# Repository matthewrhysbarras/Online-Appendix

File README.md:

# Online Appendix

Hardware and embedded firmware accompanying Matthew Rhys Barras's University of Hull PhD thesis, *Toward Mobile Neuroimaging: Design and Implementation of a Real-Time Multi-Modal EEG/fNIRS System*.

## Contents

| Directory | Contents | Thesis reference |
| --- | --- | --- |
| [Hardware](Hardware/README.md) | Revision 3 KiCad main-board project and July 2022 fabrication files | Chapter 3; Appendix A |
| [Firmware/STM32](Firmware/STM32/README.md) | STM32H743 acquisition firmware, 30 March 2022 snapshot | Chapter 4; Appendix B |
| [Firmware/ESP32](Firmware/ESP32/README.md) | ESP32-S2 communications firmware, 21 March 2022 snapshot | Chapter 4; Appendix B |

The study data path is STM32 acquisition → ESP32-S2 TCP forwarding → Python receiver → PC-side Lab Streaming Layer (LSL). The firmware retains the study packet format and optical schedule described in Chapter 4.

This repository covers the main-board design and study streaming firmware. The host application, recordings, mechanical designs and earlier development versions listed in the thesis are separate artefacts. Chapter 6's replay experiment is available as [Edge EEG Workload Classification v1.0.0](https://doi.org/10.5281/zenodo.20452990).

## Using the files

Start with the component READMEs for project layout, toolchains, configuration and build instructions. The hardware README explains how to open the KiCad project. These are research-prototype files; fabrication and participant use require appropriate engineering and safety review.

[PROVENANCE.md](PROVENANCE.md) records snapshot identifiers and preparation changes. [REVIEW.md](REVIEW.md) summarises verification. Existing attribution and licence notices are retained; see [LICENSING.md](LICENSING.md).

For citation, use the thesis title and author above, together with the relevant snapshot date or archive checksum. The thesis artefact access route is [matthewbarras.com/phd](https://matthewbarras.com/phd).

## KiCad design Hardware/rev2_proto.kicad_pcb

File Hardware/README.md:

# Revision 3 hardware

KiCad design files for the integrated EEG/fNIRS main board described in Chapter 3. The July 2022 revision 3 project retains its original filename, `rev2_proto`.

The board contains an STM32H743VIT6, an ESP32-S2-WROVER-I, four ADS1299 converters, power supplies, status indicators and interfaces for microSD storage and external optical hardware. The TLC5940 source driver connects through a daughterboard header. Tethered operation uses an external USB isolator.

## Open the project

Open `rev2_proto.kicad_pro` in KiCad, then open the schematic or PCB editor. The project contains:

- `rev2_proto.kicad_sch`: processors and board interfaces.
- `ADS1299.kicad_sch`, `ADS1299_B.kicad_sch`, `ADS1299_C.kicad_sch`, `ADS1299_D.kicad_sch`: converter sheets.
- `PowerSupplies.kicad_sch` and `Status_LEDs.kicad_sch`.
- `rev2_proto.kicad_pcb`: four-layer PCB layout.
- `Fabrication-2022-07-15/`: 13 Gerber and drill files covering copper, solder mask, paste, silkscreen, outline and plated/non-plated holes.

The project uses KiCad 6 format; the fabrication headers identify KiCad 6.0.4. Opening and exporting the project was also checked with KiCad 10.0.4. The supplied files remain in their original format.

Symbols and footprints are embedded, so the schematic and board can be inspected without restoring workstation-specific libraries. Library-based updates require the corresponding libraries. Optional external 3D models are not included, so the 3D view may be incomplete.

## Revision and use

The selected PCB is the 15 July 2022, 15:24 copy, supplied with the July fabrication outputs. Snapshot hashes and the relationship to the earlier same-day archive are recorded in [PROVENANCE.md](../PROVENANCE.md).

The circuit, layout and fabrication files are unchanged. Preparation removed temporary project files, workstation paths and an obsolete reference URL. A layer-export comparison confirmed unchanged PCB geometry.

This is the main-board project; optical daughterboards, optode assemblies and enclosure parts are separate. A fitted-component BOM is not supplied. Before fabrication, check design rules, component selection, assembly requirements and manufacturing settings. The design is a research prototype, not a clinically certified device.

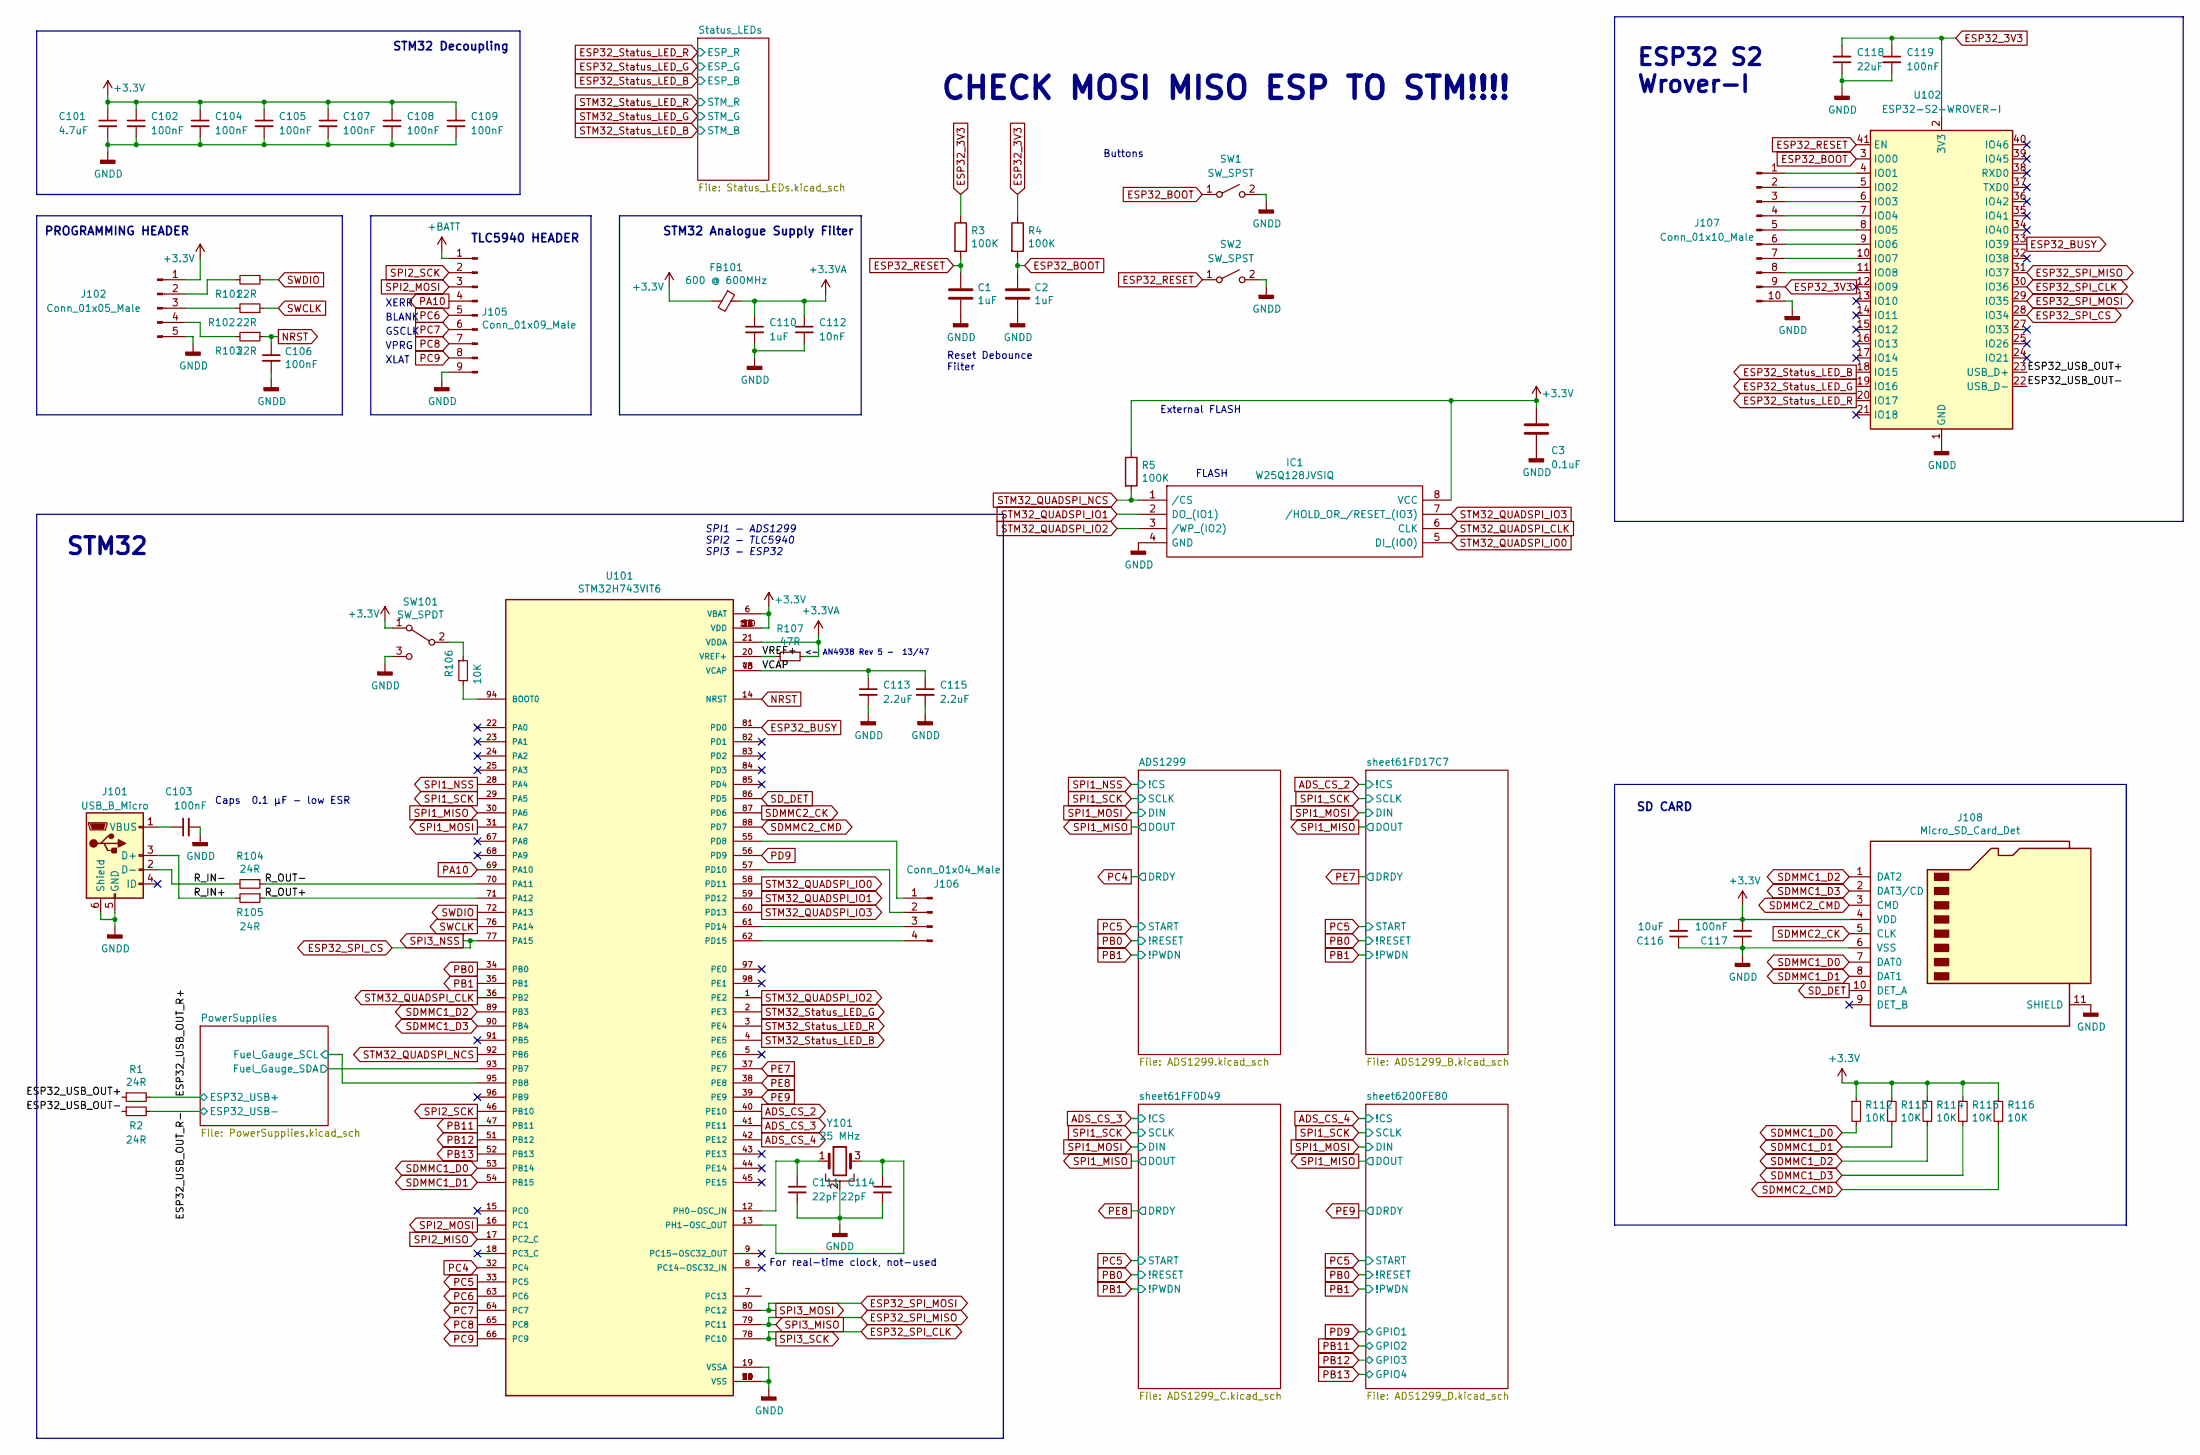
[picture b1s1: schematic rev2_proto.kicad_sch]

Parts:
C1, C2: 1uF; C_0402_1005Metric
C3: 0.1uF; C_0402_1005Metric
C101: 4.7uF; C_0805_2012Metric
C102, C103, C104, C105, C106, C107, C108, C109, C117, C119: 100nF; C_0805_2012Metric
C110: 1uF; C_0805_2012Metric
C111, C114: 22pF; C_0805_2012Metric
C112: 10nF; C_0805_2012Metric
C113, C115: 2.2uF; C_0805_2012Metric
C116: 10uF; C_0805_2012Metric
C118: 22uF; C_0805_2012Metric
FB101: 600 @ 600MHz; L_0805_2012Metric
IC1: W25Q128JVSIQ; SOIC127P790X216-8N; Mouser Part Number 454-W25Q128JVSIQ
J101: USB_B_Micro; USB_Micro-B_Wuerth_629105150521
J102: Conn_01x05_Male; PinHeader_1x05_P2.54mm_Vertical
J105: Conn_01x09_Male; PinHeader_1x09_P1.27mm_Vertical
J106: Conn_01x04_Male; PinHeader_1x04_P1.27mm_Vertical
J107: Conn_01x10_Male; PinHeader_1x10_P1.27mm_Vertical
J108: Micro_SD_Card_Det; microSD_HC_Molex_104031-0811
R1, R2, R104, R105: 24R; R_0805_2012Metric
R3, R4, R5: 100K; R_0402_1005Metric
R101, R102, R103: 22R; R_0805_2012Metric
R106, R112, R113, R114, R115, R116: 10K; R_0805_2012Metric
R107: 47R; R_0805_2012Metric
SW1, SW2: SW_SPST; SW_PUSH_6mm_H4.3mm
SW101: SW_SPDT; PinHeader_1x03_P2.54mm_Vertical
U101: STM32H743VIT6; QFP50P1600X1600X160-100N; PARTREV 7
U102: ESP32-S2-WROVER-I; ESP32-S2-WROVER
Y101: 25 MHz; Crystal_SMD_Abracon_ABM8G-4Pin_3.2x2.5mm

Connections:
+3.3VA: C110.1, C112.1, FB101.1, R107.1, U101.21 (VDDA)
+BATT: J105.1; also elsewhere on the board
/ESP32_USB_OUT+: R1.1, U102.23 (USB_D+)
/ESP32_USB_OUT-: R2.1, U102.22 (USB_D-)
/ESP32_USB_OUT_R+: R1.2; also elsewhere on the board
/ESP32_USB_OUT_R-: R2.2; also elsewhere on the board
/PowerSupplies/Fuel_Gauge_SCL: U101.95 (PB8); also elsewhere on the board
/PowerSupplies/Fuel_Gauge_SDA: U101.93 (PB7); also elsewhere on the board
/R_IN+: J101.3 (D+), R105.2
/R_IN-: J101.2 (D-), R104.2
/R_OUT+: R105.1, U101.71 (PA12)
/R_OUT-: R104.1, U101.70 (PA11)
/VCAP: C113.1, C115.1, U101.48 (VCAP), U101.73 (VCAP)
/VREF+: R107.2, U101.20 (VREF+)
ADS_CS_2: U101.40 (PE10); also elsewhere on the board
ADS_CS_3: U101.41 (PE11); also elsewhere on the board
ADS_CS_4: U101.42 (PE12); also elsewhere on the board
ESP32_3V3: C118.2, C119.1, J107.9, R3.1, R4.1, U102.2 (3V3); also elsewhere on the board
ESP32_BOOT: C2.1, R4.2, SW1.1 (A), U102.3 (IO00); also elsewhere on the board
ESP32_BUSY: U101.81 (PD0), U102.33 (IO39)
ESP32_RESET: C1.1, R3.2, SW2.1 (A), U102.41 (EN); also elsewhere on the board
ESP32_SPI_CLK: U101.78 (PC10), U102.30 (IO36)
ESP32_SPI_CS: U101.77 (PA15), U102.28 (IO34)
ESP32_SPI_MISO: U101.79 (PC11), U102.31 (IO37)
ESP32_SPI_MOSI: U101.80 (PC12), U102.29 (IO35)
ESP32_Status_LED_B: U102.18 (IO15); also elsewhere on the board
ESP32_Status_LED_G: U102.19 (IO16); also elsewhere on the board
ESP32_Status_LED_R: U102.20 (IO17); also elsewhere on the board
GNDA: C1.2, C2.2, C3.2, C101.2, C102.2, C103.2, C104.2, C105.2, C106.2, C107.2, C108.2, C109.2, C110.2, C111.2, C112.2, C113.2, C114.2, C115.2, C116.1, C117.1, C118.1, C119.2, IC1.4 (GND), J101.5 (GND), J101.6 (Shield), J102.5, J105.9, J107.10, J108.6 (VSS), J108.11 (SHIELD), SW1.2 (B), SW2.2 (B), SW101.3 (C), U101.10 (VSS), U101.19 (VSSA), U101.26 (VSS), U101.49 (VSS), U101.74 (VSS), U101.99 (VSS), U102.1 (GND), U102.26 (GND), U102.42 (GND), U102.43 (GND), Y101.2; also elsewhere on the board
NRST: C106.1, R103.1, U101.14 (NRST)
unnamed: C103.1, J101.1 (VBUS)
unnamed: C111.1, U101.12 (PH0-OSC_IN), Y101.1
unnamed: C114.1, U101.13 (PH1-OSC_OUT), Y101.3
unnamed: J102.2, R101.2
unnamed: J102.3, R102.2
unnamed: J102.4, R103.2
unnamed: J106.1, U101.55 (PD8)
unnamed: J106.2, U101.57 (PD10)
unnamed: J106.3, U101.61 (PD14)
unnamed: J106.4, U101.62 (PD15)
unnamed: J107.1, U102.4 (IO01)
unnamed: J107.2, U102.5 (IO02)
unnamed: J107.3, U102.6 (IO03)
unnamed: J107.4, U102.7 (IO04)
unnamed: J107.5, U102.8 (IO05)
unnamed: J107.6, U102.9 (IO06)
unnamed: J107.7, U102.10 (IO07)
unnamed: J107.8, U102.11 (IO08)
unnamed: R106.1, SW101.2 (B)
unnamed: R106.2, U101.94 (BOOT0)
PA10: J105.4, U101.69 (PA10)
PB0: U101.34 (PB0); also elsewhere on the board
PB1: U101.35 (PB1); also elsewhere on the board
PB11: U101.47 (PB11); also elsewhere on the board
PB12: U101.51 (PB12); also elsewhere on the board
PB13: U101.52 (PB13); also elsewhere on the board
PC4: U101.32 (PC4); also elsewhere on the board
PC5: U101.33 (PC5); also elsewhere on the board
PC6: J105.5, U101.63 (PC6)
PC7: J105.6, U101.64 (PC7)
PC8: J105.7, U101.65 (PC8)
PC9: J105.8, U101.66 (PC9)
PD9: U101.56 (PD9); also elsewhere on the board
PE7: U101.37 (PE7); also elsewhere on the board
PE8: U101.38 (PE8); also elsewhere on the board
PE9: U101.39 (PE9); also elsewhere on the board
SDMMC1_D0: J108.7 (DAT0), R112.2, U101.53 (PB14)
SDMMC1_D1: J108.8 (DAT1), R113.2, U101.54 (PB15)
SDMMC1_D2: J108.1 (DAT2), R114.2, U101.89 (PB3)
SDMMC1_D3: J108.2 (DAT3/CD), R115.2, U101.90 (PB4)
SDMMC2_CK: J108.5 (CLK), U101.87 (PD6)
SDMMC2_CMD: J108.3 (CMD), R116.2, U101.88 (PD7)
SD_DET: J108.10 (DET_A), U101.86 (PD5)
SPI1_MISO: U101.30 (PA6); also elsewhere on the board
SPI1_MOSI: U101.31 (PA7); also elsewhere on the board
SPI1_NSS: U101.28 (PA4); also elsewhere on the board
SPI1_SCK: U101.29 (PA5); also elsewhere on the board
SPI2_MISO: U101.17 (PC2_C)
SPI2_MOSI: J105.3, U101.16 (PC1)
SPI2_SCK: J105.2, U101.46 (PB10)
STM32_QUADSPI_CLK: IC1.6 (CLK), U101.36 (PB2)
STM32_QUADSPI_IO0: IC1.5 (DI_(IO0)), U101.58 (PD11)
STM32_QUADSPI_IO1: IC1.2 (DO_(IO1)), U101.59 (PD12)
STM32_QUADSPI_IO2: IC1.3 (/WP_(IO2)), U101.1 (PE2)
STM32_QUADSPI_IO3: IC1.7 (/HOLD_OR_/RESET_(IO3)), U101.60 (PD13)
STM32_QUADSPI_NCS: IC1.1 (/CS), R5.2, U101.92 (PB6)
STM32_Status_LED_B: U101.4 (PE5); also elsewhere on the board
STM32_Status_LED_G: U101.2 (PE3); also elsewhere on the board
STM32_Status_LED_R: U101.3 (PE4); also elsewhere on the board
SWCLK: R102.1, U101.76 (PA14)
SWDIO: R101.1, U101.72 (PA13)

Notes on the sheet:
SD CARD
CHECK MOSI MISO ESP TO STM!!!!
Buttons
VPRG
ESP32 S2 Wrover-I
XERR
FLASH
Reset Debounce Filter
SPI1 - ADS1299 SPI2 - TLC5940 SPI3 - ESP32
XLAT
For real-time clock, not-used
TLC5940 HEADER
External FLASH
BLANK
<- AN4938 Rev 5 - 13/47
STM32 Analogue Supply Filter
STM32 Decoupling
GSCLK
PROGRAMMING HEADER
Caps 0.1 μF - low ESR
STM32

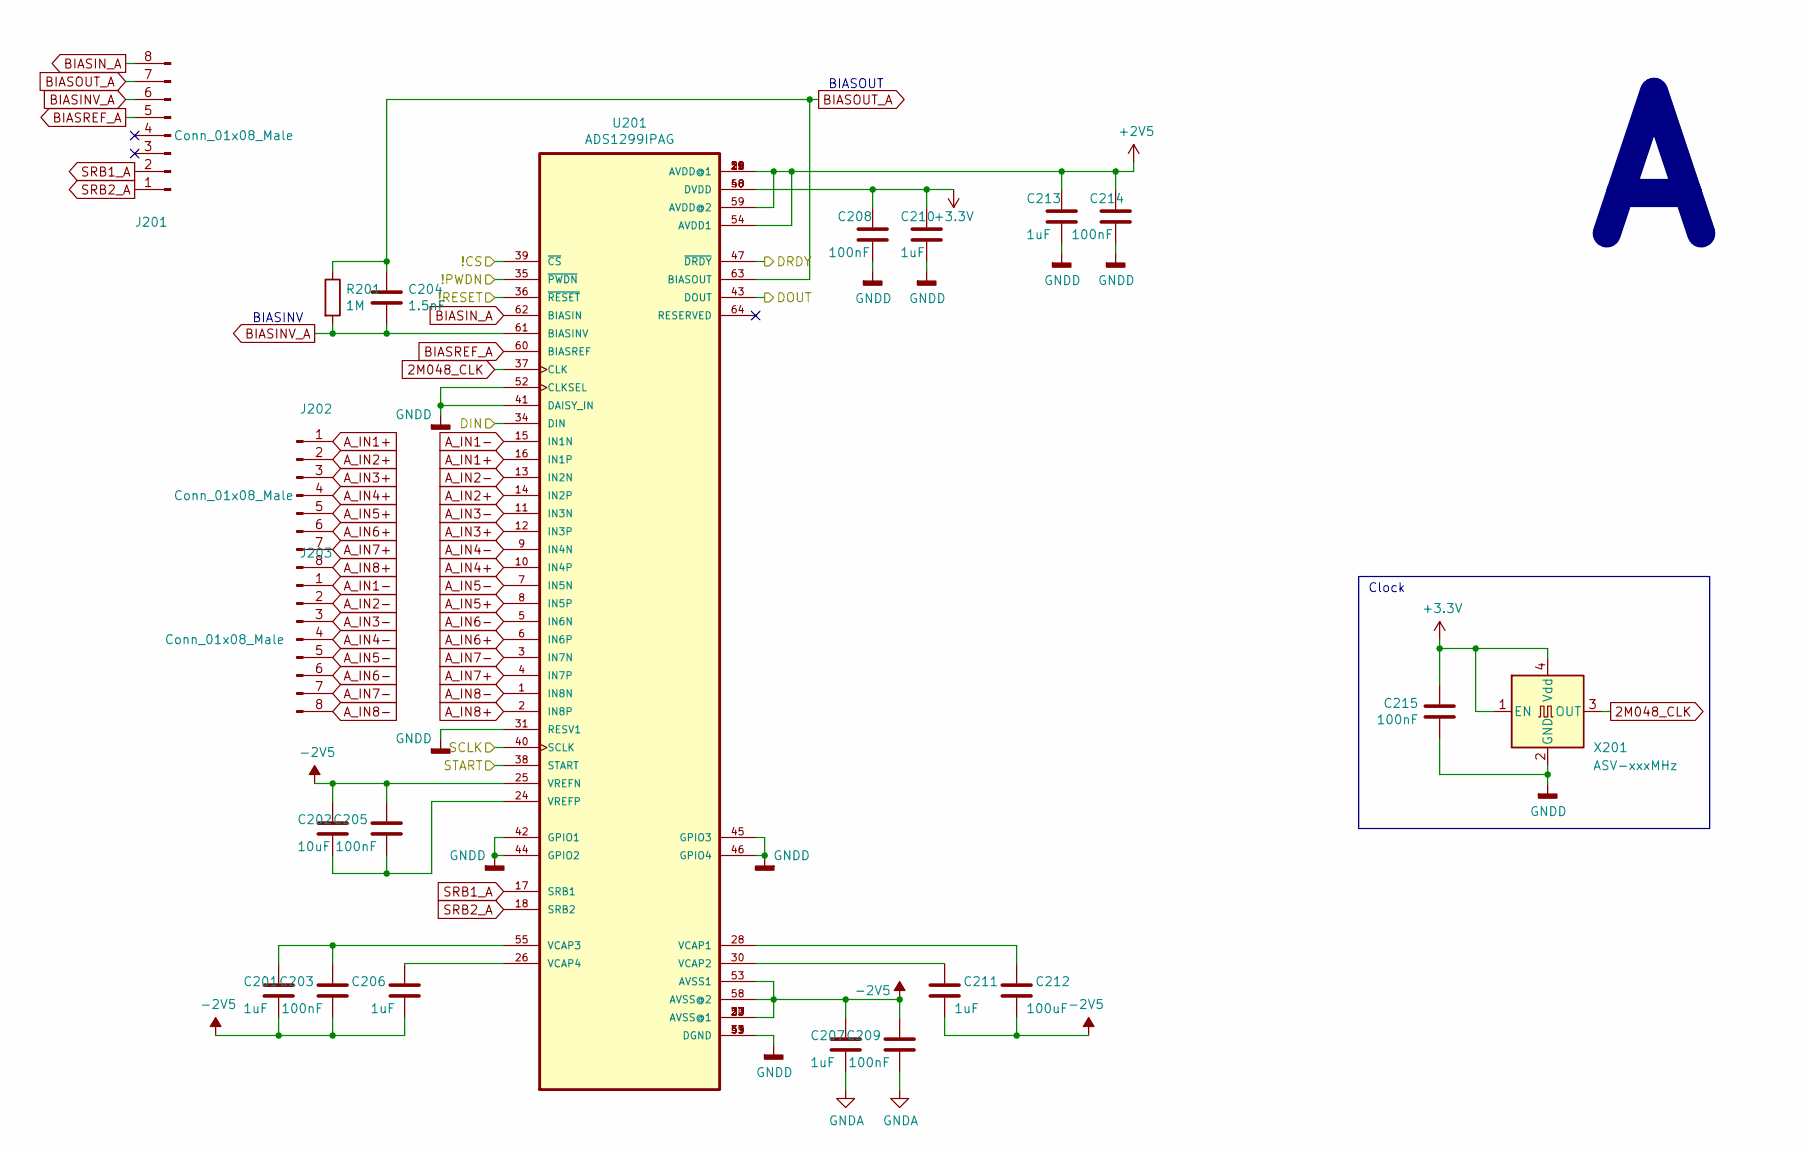
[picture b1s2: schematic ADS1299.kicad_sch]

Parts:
C201, C206, C207, C210, C211, C213: 1uF; C_0805_2012Metric
C202: 10uF; C_0805_2012Metric
C203, C205, C208, C209, C214, C215: 100nF; C_0805_2012Metric
C204: 1.5nF; C_0805_2012Metric
C212: 100uF; C_0805_2012Metric
J201, J202, J203: Conn_01x08_Male; PinHeader_1x08_P2.54mm_Vertical
R201: 1M; R_0805_2012Metric
U201: ADS1299IPAG; QFP50P1200X1200X120-64N
X201: ASV-xxxMHz; Oscillator_SMD_Abracon_ASV-4Pin_7.0x5.1mm

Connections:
2M048_CLK: U201.37 (CLK), X201.3 (OUT); also elsewhere on the board
+2V5: C213.1, C214.1, U201.19 (AVDD@1), U201.21 (AVDD@1), U201.22 (AVDD@1), U201.54 (AVDD1), U201.56 (AVDD@1), U201.59 (AVDD@2); also elsewhere on the board
-2V5: C201.2, C202.1, C203.2, C205.1, C206.2, C207.1, C209.1, C211.2, C212.2, U201.20 (AVSS@1), U201.23 (AVSS@1), U201.25 (VREFN), U201.32 (AVSS@1), U201.53 (AVSS1), U201.57 (AVSS@1), U201.58 (AVSS@2); also elsewhere on the board
A_IN1+: J202.1, U201.16 (IN1P)
A_IN1-: J203.1, U201.15 (IN1N)
A_IN2+: J202.2, U201.14 (IN2P)
A_IN2-: J203.2, U201.13 (IN2N)
A_IN3+: J202.3, U201.12 (IN3P)
A_IN3-: J203.3, U201.11 (IN3N)
A_IN4+: J202.4, U201.10 (IN4P)
A_IN4-: J203.4, U201.9 (IN4N)
A_IN5+: J202.5, U201.8 (IN5P)
A_IN5-: J203.5, U201.7 (IN5N)
A_IN6+: J202.6, U201.6 (IN6P)
A_IN6-: J203.6, U201.5 (IN6N)
A_IN7+: J202.7, U201.4 (IN7P)
A_IN7-: J203.7, U201.3 (IN7N)
A_IN8+: J202.8, U201.2 (IN8P)
A_IN8-: J203.8, U201.1 (IN8N)
BIASINV_A: C204.2, J201.6, R201.2, U201.61 (BIASINV)
BIASIN_A: J201.8, U201.62 (BIASIN)
BIASOUT_A: C204.1, J201.7, R201.1, U201.63 (BIASOUT)
BIASREF_A: J201.5, U201.60 (BIASREF)
GNDA: C207.2, C208.2, C209.2, C210.2, C213.2, C214.2, C215.1, U201.31 (RESV1), U201.33 (DGND), U201.41 (DAISY_IN), U201.42 (GPIO1), U201.44 (GPIO2), U201.45 (GPIO3), U201.46 (GPIO4), U201.49 (DGND), U201.51 (DGND), U201.52 (CLKSEL), X201.2 (GND); also elsewhere on the board
unnamed: C201.1, C203.1, U201.55 (VCAP3)
unnamed: C202.2, C205.2, U201.24 (VREFP)
unnamed: C206.1, U201.26 (VCAP4)
unnamed: C211.1, U201.30 (VCAP2)
unnamed: C212.1, U201.28 (VCAP1)
PB0: U201.36 (~RESET); also elsewhere on the board
PB1: U201.35 (~PWDN); also elsewhere on the board
PC4: U201.47 (~DRDY); also elsewhere on the board
PC5: U201.38 (START); also elsewhere on the board
SPI1_MISO: U201.43 (DOUT); also elsewhere on the board
SPI1_MOSI: U201.34 (DIN); also elsewhere on the board
SPI1_NSS: U201.39 (~CS); also elsewhere on the board
SPI1_SCK: U201.40 (SCLK); also elsewhere on the board
SRB1_A: J201.2, U201.17 (SRB1)
SRB2_A: J201.1, U201.18 (SRB2)

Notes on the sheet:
BIASOUT
BIASINV
Clock

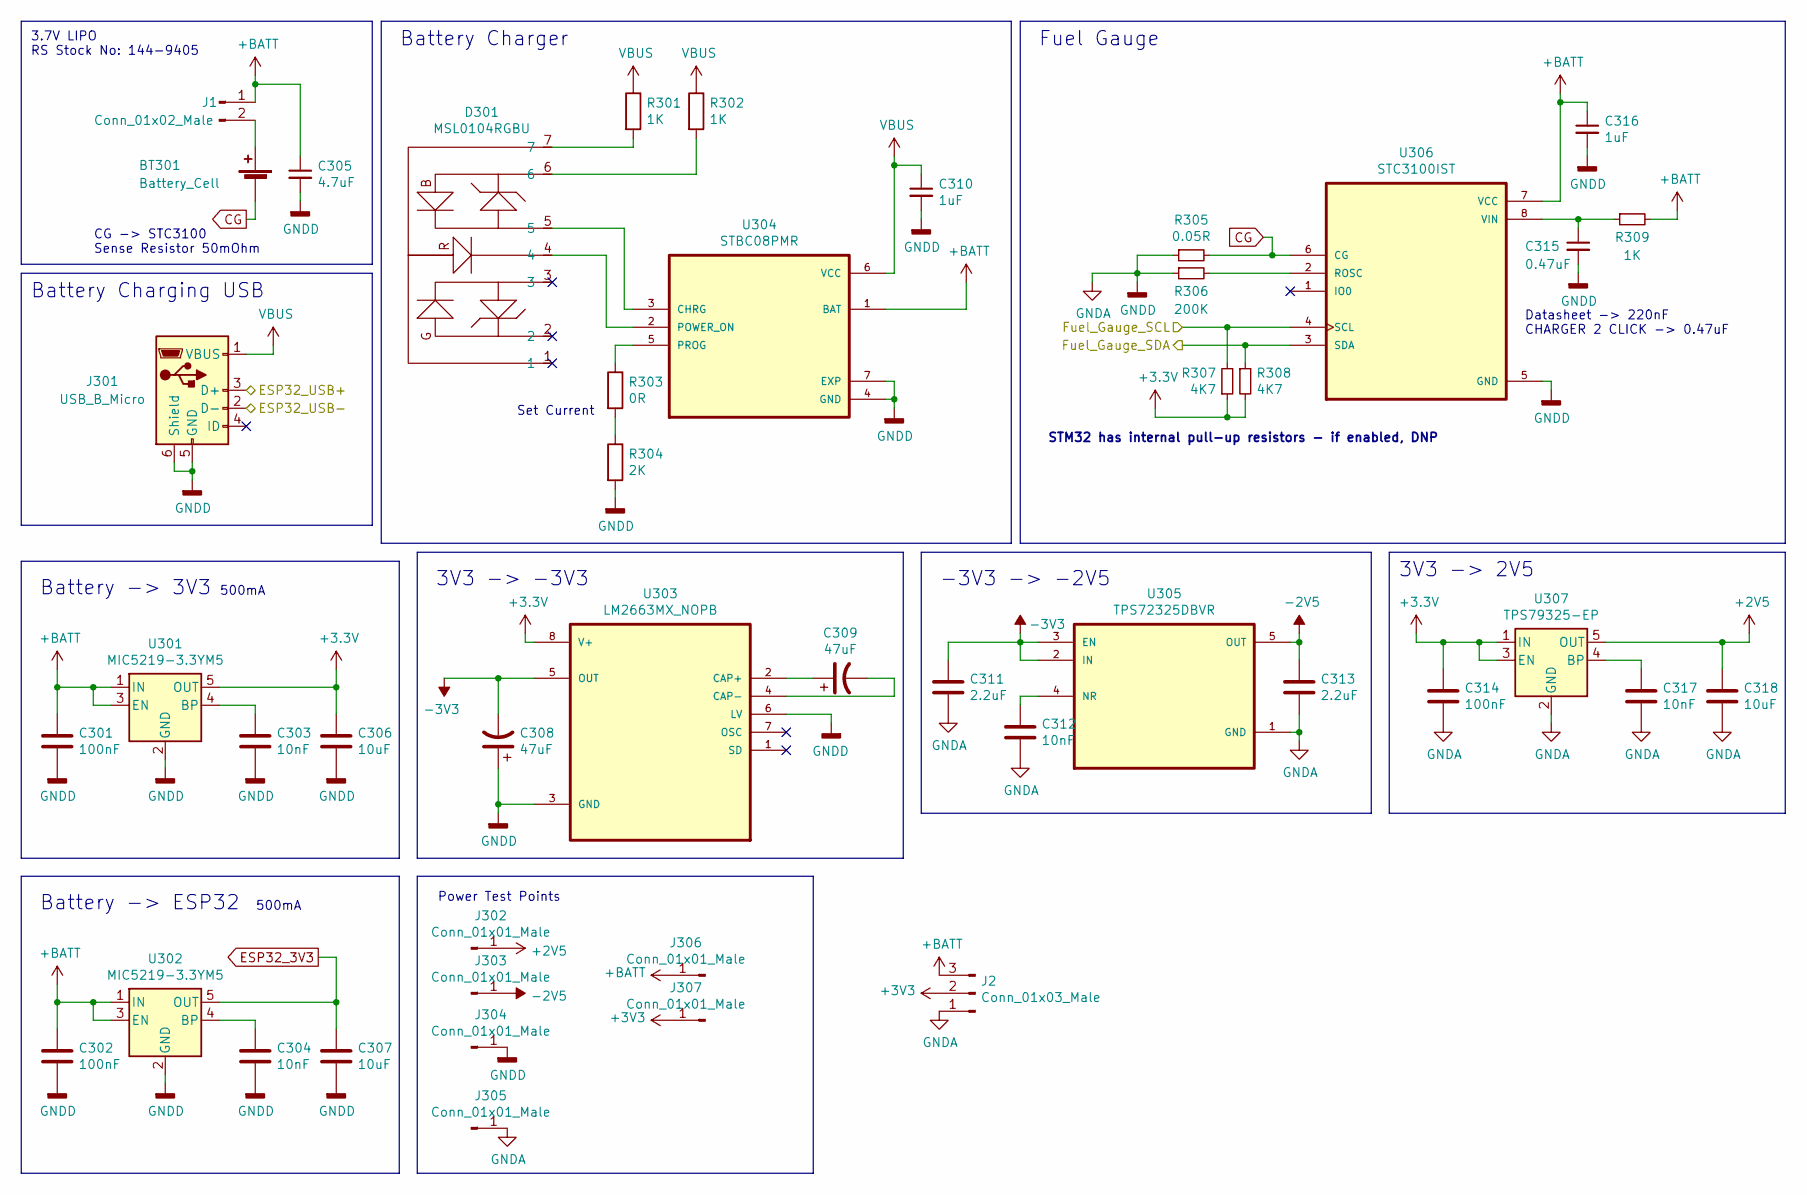
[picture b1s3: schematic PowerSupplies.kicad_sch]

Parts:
BT301: Battery_Cell; PinHeader_1x02_P2.54mm_Vertical
C301, C302, C314: 100nF; C_0805_2012Metric
C303, C304, C312, C317: 10nF; C_0805_2012Metric
C305: 4.7uF; C_0805_2012Metric
C306, C307, C318: 10uF; C_0805_2012Metric
C308, C309: 47uF; C_0805_2012Metric
C310, C316: 1uF; C_0805_2012Metric
C311, C313: 2.2uF; C_0805_2012Metric
C315: 0.47uF; C_0805_2012Metric
D301: MSL0104RGBU; MSL0104RGB
J1: Conn_01x02_Male; PinHeader_1x02_P2.54mm_Vertical
J2: Conn_01x03_Male; PinHeader_1x03_P2.54mm_Vertical
J301: USB_B_Micro; USB_Micro-B_Wuerth_629105150521
J302, J303, J305, J306, J307: Conn_01x01_Male; TestPoint_Pad_D1.0mm
J304: Conn_01x01_Male; TestPoint_Pad_3.0x3.0mm
R301, R302, R309: 1K; R_0805_2012Metric
R303: 0R; R_0805_2012Metric
R304: 2K; R_0805_2012Metric
R305: 0.05R; R_0805_2012Metric
R306: 200K; R_0805_2012Metric
R307, R308: 4K7; R_0805_2012Metric
U301, U302: MIC5219-3.3YM5; SOT-23-5
U303: LM2663MX_NOPB; SOIC127P599X175-8N
U304: STBC08PMR; SON95P300X300X100-7N; PARTREV 4
U305: TPS72325DBVR; SOT95P280X145-5N
U306: STC3100IST; SOIC65P490X110-8N
U307: TPS79325-EP; SOT-23-5

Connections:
+2V5: C318.1, J302.1, U307.5 (OUT); also elsewhere on the board
+BATT: C301.1, C302.1, C305.1, C316.1, J1.1, J2.3, J306.1, R309.2, U301.1 (IN), U301.3 (EN), U302.1 (IN), U302.3 (EN), U304.1 (BAT), U306.7 (VCC); also elsewhere on the board
-2V5: C313.1, J303.1, U305.5 (OUT); also elsewhere on the board
-3V3: C308.2, C311.1, U303.5 (OUT), U305.2 (IN), U305.3 (EN)
/ESP32_USB_OUT_R+: J301.3 (D+); also elsewhere on the board
/ESP32_USB_OUT_R-: J301.2 (D-); also elsewhere on the board
/PowerSupplies/Fuel_Gauge_SCL: R307.2, U306.4 (SCL); also elsewhere on the board
/PowerSupplies/Fuel_Gauge_SDA: R308.1, U306.3 (SDA); also elsewhere on the board
CG: BT301.2 (-), R305.2, U306.6 (CG)
ESP32_3V3: C307.1, U302.5 (OUT); also elsewhere on the board
GNDA: C301.2, C302.2, C303.2, C304.2, C305.2, C306.2, C307.2, C308.1, C310.2, C311.2, C312.2, C313.2, C314.2, C315.2, C316.2, C317.2, C318.2, J2.1, J301.5 (GND), J301.6 (Shield), J304.1, J305.1, R304.2, R305.1, R306.1, U301.2 (GND), U302.2 (GND), U303.3 (GND), U303.6 (LV), U304.4 (GND), U304.7 (EXP), U305.1 (GND), U306.5 (GND), U307.2 (GND); also elsewhere on the board
unnamed: BT301.1 (+), J1.2
unnamed: C303.1, U301.4 (BP)
unnamed: C304.1, U302.4 (BP)
unnamed: C309.1, U303.2 (CAP+)
unnamed: C309.2, U303.4 (CAP-)
unnamed: C312.1, U305.4 (NR)
unnamed: C315.1, R309.1, U306.8 (VIN)
unnamed: C317.1, U307.4 (BP)
unnamed: D301.4, U304.2 (POWER_ON)
unnamed: D301.5, U304.3 (CHRG)
unnamed: D301.6, R302.2
unnamed: D301.7, R301.2
unnamed: R303.1, U304.5 (PROG)
unnamed: R303.2, R304.1
unnamed: R306.2, U306.2 (ROSC)
VBUS: C310.1, J301.1 (VBUS), R301.1, R302.1, U304.6 (VCC)

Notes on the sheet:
500mA
Battery Charger
3.7V LIPO RS Stock No: 144-9405
CG -> STC3100 Sense Resistor 50mOhm
3V3 -> -3V3
Battery Charging USB
Fuel Gauge
Battery -> ESP32
Power Test Points
-3V3 -> -2V5
STM32 has internal pull-up resistors - if enabled, DNP
3V3 -> 2V5
Datasheet -> 220nF CHARGER 2 CLICK -> 0.47uF
Set Current
Battery -> 3V3

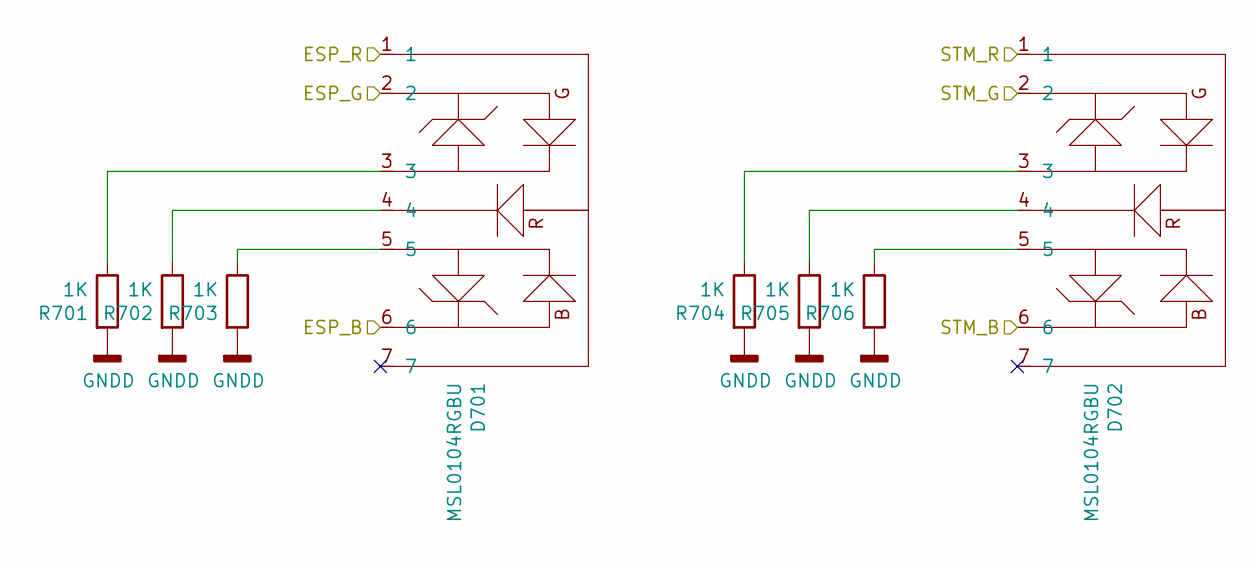
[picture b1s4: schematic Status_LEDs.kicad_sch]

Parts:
D701, D702: MSL0104RGBU; MSL0104RGB
R701, R702, R703, R704, R705, R706: 1K; R_0805_2012Metric

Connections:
ESP32_Status_LED_B: D701.6; also elsewhere on the board
ESP32_Status_LED_G: D701.2; also elsewhere on the board
ESP32_Status_LED_R: D701.1; also elsewhere on the board
GNDA: R701.2, R702.2, R703.2, R704.2, R705.2, R706.2; also elsewhere on the board
unnamed: D701.3, R701.1
unnamed: D701.4, R702.1
unnamed: D701.5, R703.1
unnamed: D702.3, R704.1
unnamed: D702.4, R705.1
unnamed: D702.5, R706.1
STM32_Status_LED_B: D702.6; also elsewhere on the board
STM32_Status_LED_G: D702.2; also elsewhere on the board
STM32_Status_LED_R: D702.1; also elsewhere on the board

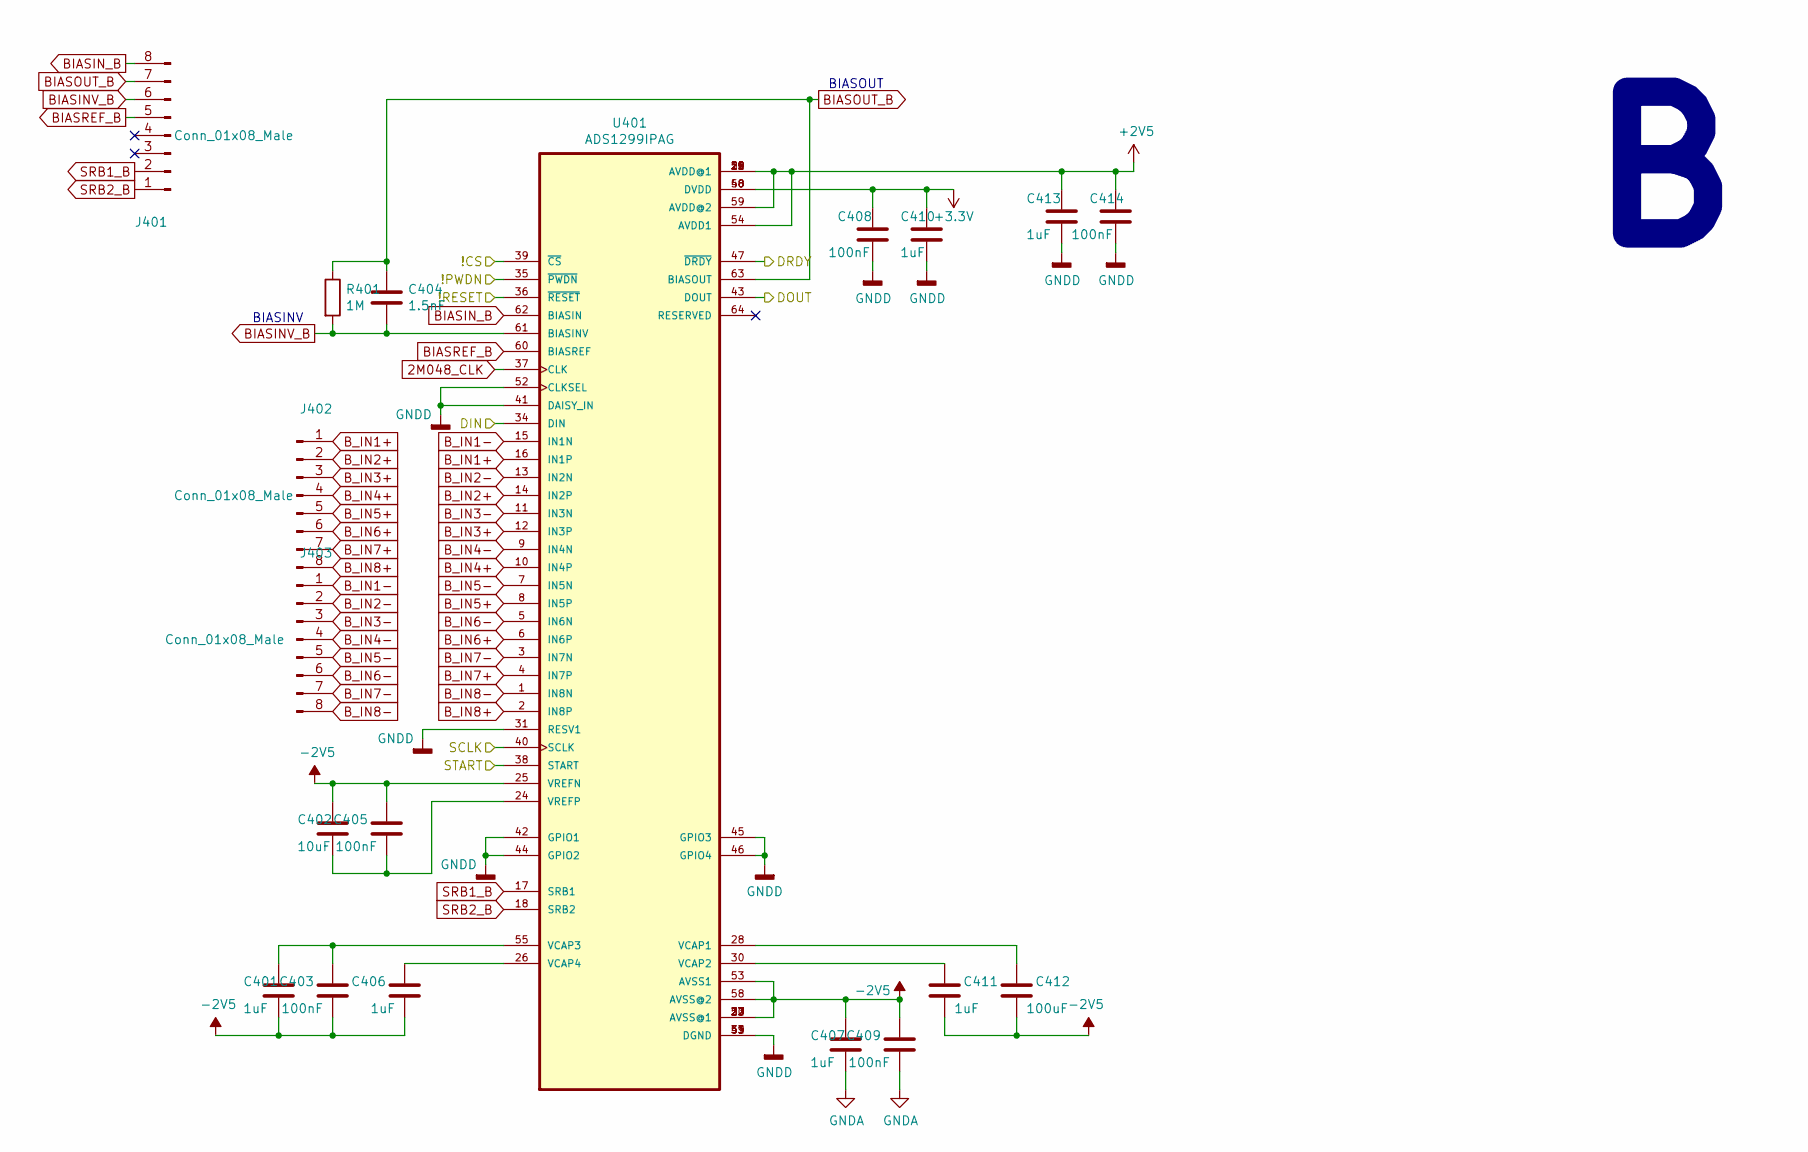
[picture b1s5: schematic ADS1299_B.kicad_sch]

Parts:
C401, C406, C407, C410, C411, C413: 1uF; C_0805_2012Metric
C402: 10uF; C_0805_2012Metric
C403, C405, C408, C409, C414: 100nF; C_0805_2012Metric
C404: 1.5nF; C_0805_2012Metric
C412: 100uF; C_0805_2012Metric
J401, J402, J403: Conn_01x08_Male; PinHeader_1x08_P2.54mm_Vertical
R401: 1M; R_0805_2012Metric
U401: ADS1299IPAG; QFP50P1200X1200X120-64N

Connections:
2M048_CLK: U401.37 (CLK); also elsewhere on the board
+2V5: C413.1, C414.1, U401.19 (AVDD@1), U401.21 (AVDD@1), U401.22 (AVDD@1), U401.54 (AVDD1), U401.56 (AVDD@1), U401.59 (AVDD@2); also elsewhere on the board
-2V5: C401.2, C402.1, C403.2, C405.1, C406.2, C407.1, C409.1, C411.2, C412.2, U401.20 (AVSS@1), U401.23 (AVSS@1), U401.25 (VREFN), U401.32 (AVSS@1), U401.53 (AVSS1), U401.57 (AVSS@1), U401.58 (AVSS@2); also elsewhere on the board
ADS_CS_2: U401.39 (~CS); also elsewhere on the board
BIASINV_B: C404.2, J401.6, R401.2, U401.61 (BIASINV)
BIASIN_B: J401.8, U401.62 (BIASIN)
BIASOUT_B: C404.1, J401.7, R401.1, U401.63 (BIASOUT)
BIASREF_B: J401.5, U401.60 (BIASREF)
B_IN1+: J402.1, U401.16 (IN1P)
B_IN1-: J403.1, U401.15 (IN1N)
B_IN2+: J402.2, U401.14 (IN2P)
B_IN2-: J403.2, U401.13 (IN2N)
B_IN3+: J402.3, U401.12 (IN3P)
B_IN3-: J403.3, U401.11 (IN3N)
B_IN4+: J402.4, U401.10 (IN4P)
B_IN4-: J403.4, U401.9 (IN4N)
B_IN5+: J402.5, U401.8 (IN5P)
B_IN5-: J403.5, U401.7 (IN5N)
B_IN6+: J402.6, U401.6 (IN6P)
B_IN6-: J403.6, U401.5 (IN6N)
B_IN7+: J402.7, U401.4 (IN7P)
B_IN7-: J403.7, U401.3 (IN7N)
B_IN8+: J402.8, U401.2 (IN8P)
B_IN8-: J403.8, U401.1 (IN8N)
GNDA: C407.2, C408.2, C409.2, C410.2, C413.2, C414.2, U401.31 (RESV1), U401.33 (DGND), U401.41 (DAISY_IN), U401.42 (GPIO1), U401.44 (GPIO2), U401.45 (GPIO3), U401.46 (GPIO4), U401.49 (DGND), U401.51 (DGND), U401.52 (CLKSEL); also elsewhere on the board
unnamed: C401.1, C403.1, U401.55 (VCAP3)
unnamed: C402.2, C405.2, U401.24 (VREFP)
unnamed: C406.1, U401.26 (VCAP4)
unnamed: C411.1, U401.30 (VCAP2)
unnamed: C412.1, U401.28 (VCAP1)
PB0: U401.36 (~RESET); also elsewhere on the board
PB1: U401.35 (~PWDN); also elsewhere on the board
PC5: U401.38 (START); also elsewhere on the board
PE7: U401.47 (~DRDY); also elsewhere on the board
SPI1_MISO: U401.43 (DOUT); also elsewhere on the board
SPI1_MOSI: U401.34 (DIN); also elsewhere on the board
SPI1_SCK: U401.40 (SCLK); also elsewhere on the board
SRB1_B: J401.2, U401.17 (SRB1)
SRB2_B: J401.1, U401.18 (SRB2)

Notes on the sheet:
BIASINV
BIASOUT
